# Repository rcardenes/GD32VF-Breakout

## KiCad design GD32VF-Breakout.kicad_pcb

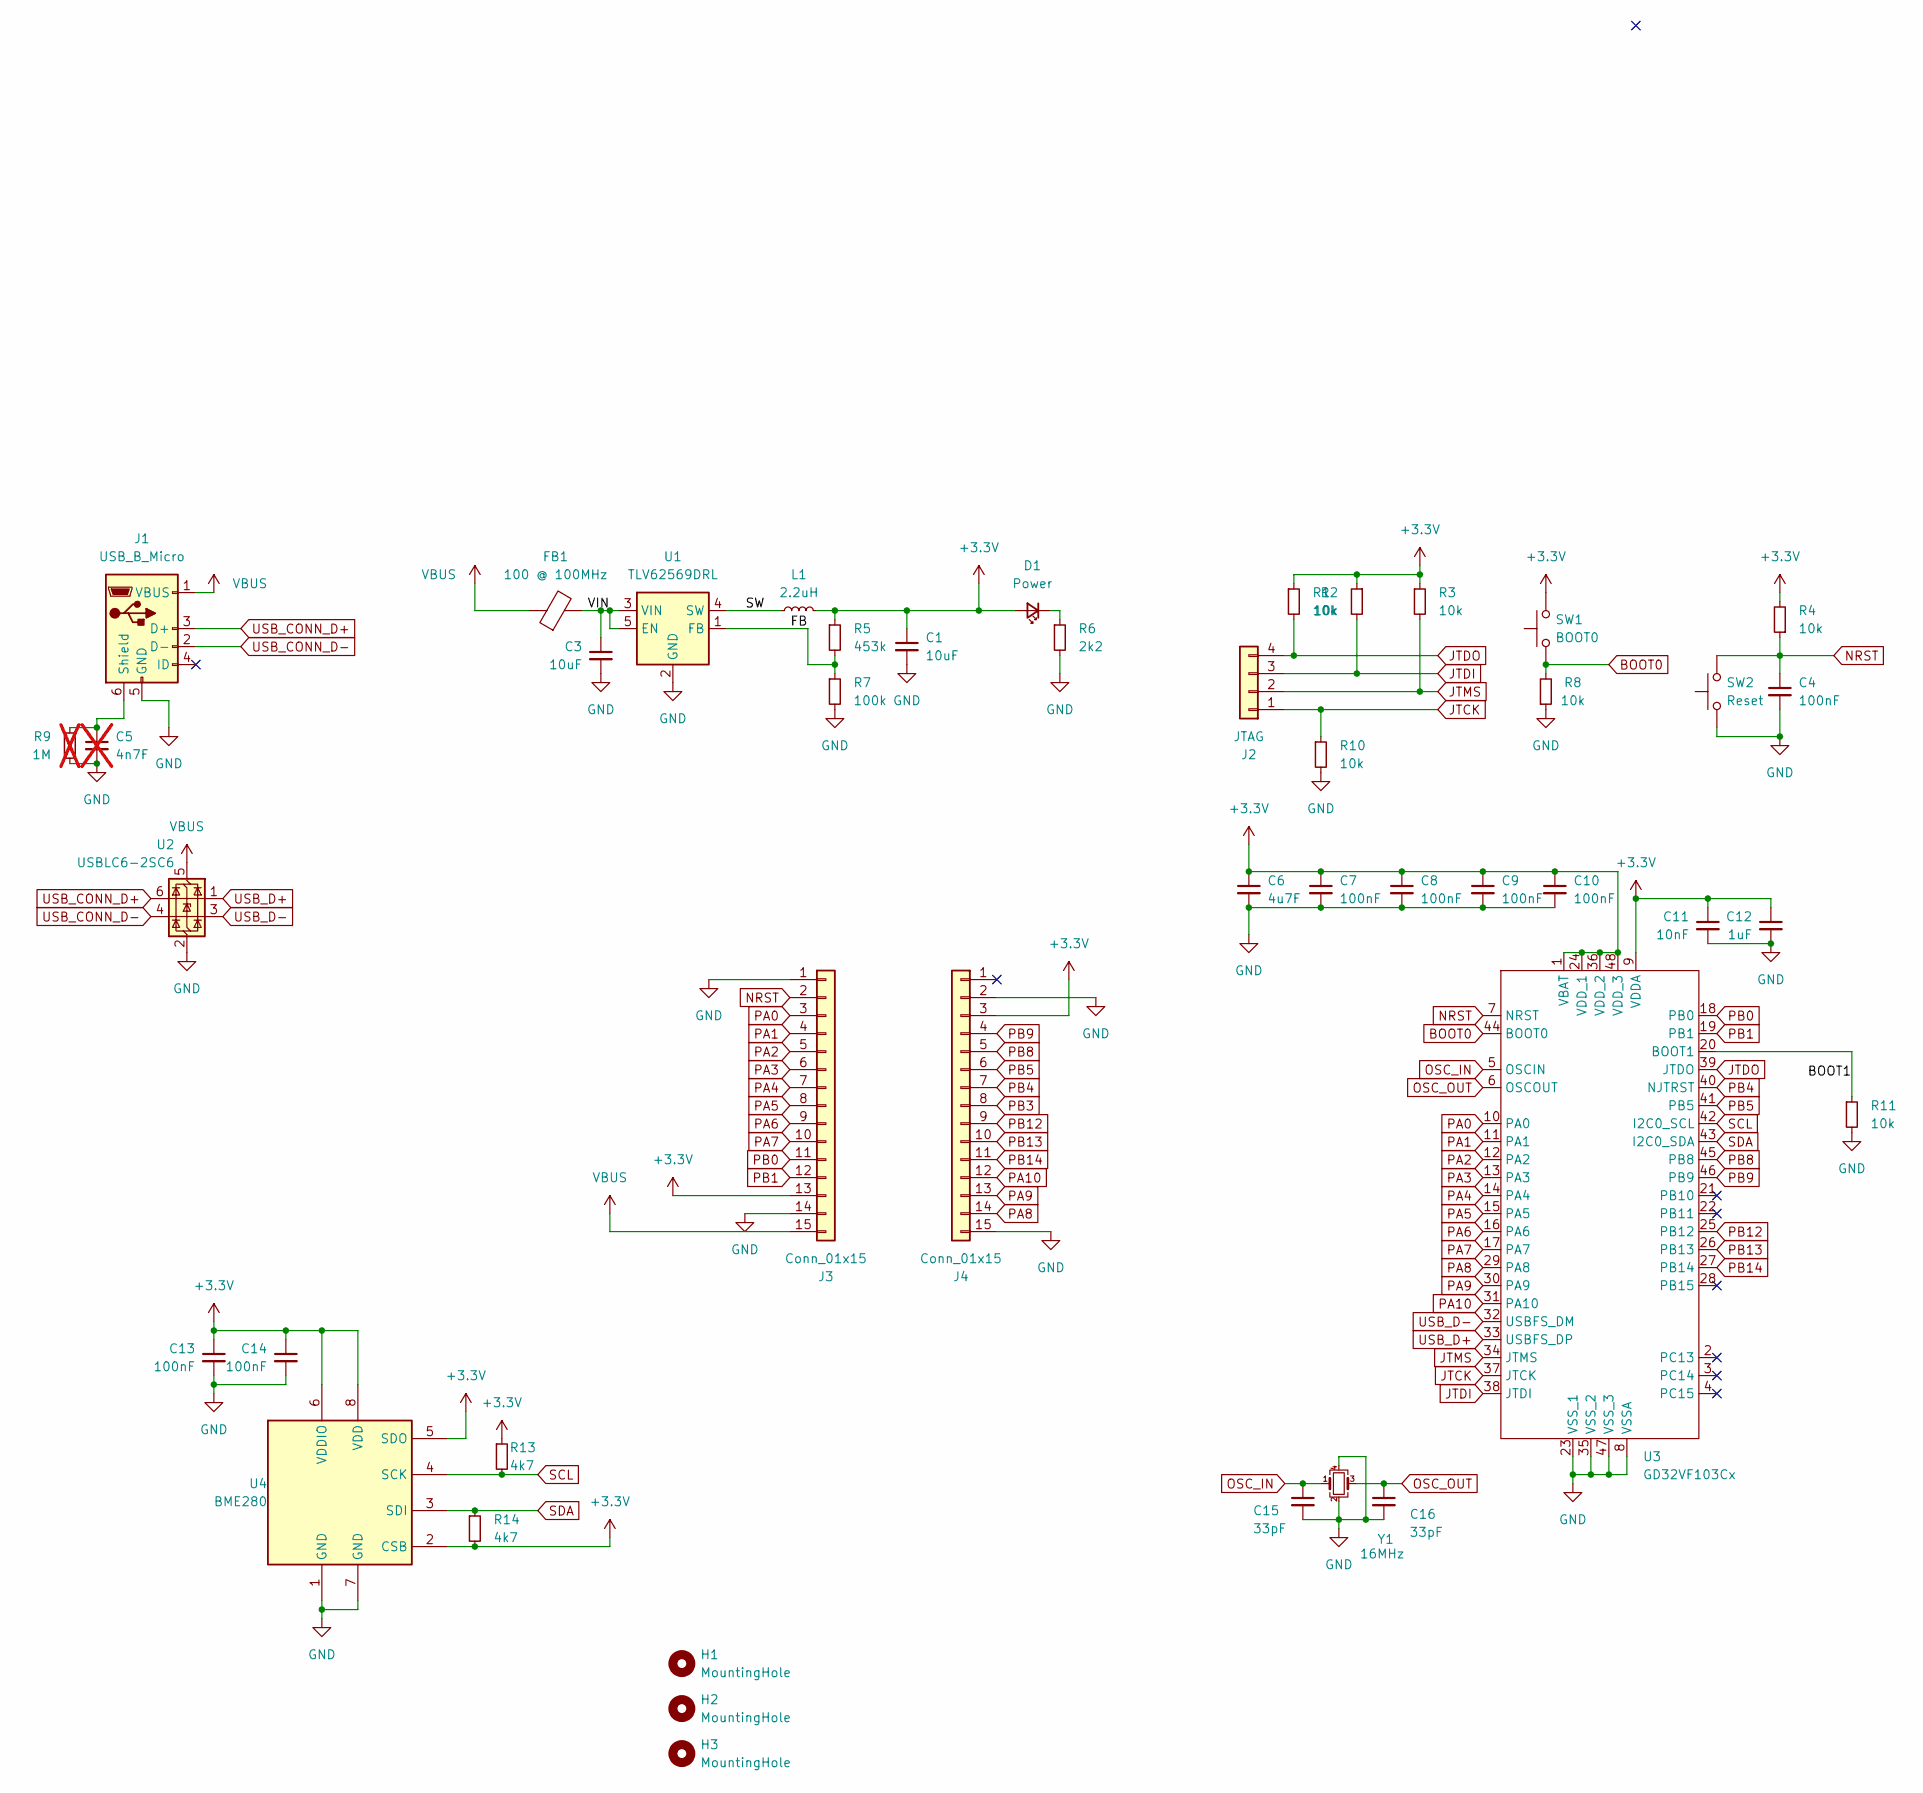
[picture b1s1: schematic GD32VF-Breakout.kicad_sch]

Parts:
C1, C3: 10uF; C_0603_1608Metric; LCSC C19702
C4: 100nF; C_0603_1608Metric; LCSC C1525
C5: 4n7F; C_0603_1608Metric; LCSC C1538; not fitted
C6: 4u7F; C_0603_1608Metric; LCSC C19666
C7, C8, C9, C10: 100nF; C_0402_1005Metric; LCSC C1525
C11: 10nF; C_0402_1005Metric; LCSC C15195
C12: 1uF; C_0603_1608Metric; LCSC C15849
C13, C14: 100nF; C_0402_1005Metric
C15, C16: 33pF; C_0603_1608Metric; LCSC C1554
D1: Power; LED_0805_2012Metric; LCSC C2286
FB1: 100 @ 100MHz; L_1206_3216Metric; LCSC C1015
H1, H2, H3: MountingHole; MountingHole_2.2mm_M2
J1: USB_B_Micro; USB_Micro-B_Amphenol_10118193-0001LF_Horizontal
J2: JTAG; PinHeader_1x04_P2.54mm_Vertical
J3, J4: Conn_01x15; PinHeader_1x15_P2.54mm_Vertical
L1: 2.2uH; L_1210_3225Metric
R1, R2, R3, R10: 10k; R_0603_1608Metric
R4, R8, R11: 10k; R_0603_1608Metric; LCSC C25744
R5: 453k; R_0603_1608Metric
R6: 2k2; R_0603_1608Metric; LCSC C25879
R7: 100k; R_0603_1608Metric
R9: 1M; R_0603_1608Metric; LCSC C26083; not fitted
R13, R14: 4k7; R_0402_1005Metric
SW1: BOOT0; SW_Push_1P1T_NO_CK_KMR2; LCSC C221676
SW2: Reset; SW_Push_1P1T_NO_CK_KMR2; LCSC C221676
U1: TLV62569DRL; SOT-563
U2: USBLC6-2SC6; SOT-23-6; LCSC C2827654
U3: GD32VF103Cx; LQFP-48_7x7mm_P0.5mm
U4: BME280; Bosch_LGA-8_2.5x2.5mm_P0.65mm_ClockwisePinNumbering
Y1: 16MHz; Crystal_SMD_3225-4Pin_3.2x2.5mm; LCSC C9002

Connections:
+3.3V: C1.1, C6.1, C7.1, C8.1, C9.1, C10.1, C11.1, C12.1, C13.1, C14.1, D1.2 (A), J3.13, J4.3, L1.2, R1.1, R2.1, R3.1, R4.2, R5.1, R13.1, R14.2, SW1.2, U3.1 (VBAT), U3.9 (VDDA), U3.24 (VDD_1), U3.36 (VDD_2), U3.48 (VDD_3), U4.2 (CSB), U4.5 (SDO), U4.6 (VDDIO), U4.8 (VDD)
/BOOT1: R11.1, U3.20 (BOOT1)
/FB: R5.2, R7.1, U1.1 (FB)
/SW: L1.1, U1.4 (SW)
/VIN: C3.1, FB1.2, U1.3 (VIN), U1.5 (EN)
BOOT0: R8.2, SW1.1, U3.44 (BOOT0)
GND: C1.2, C3.2, C4.2, C5.2, C6.2, C7.2, C8.2, C9.2, C10.2, C11.2, C12.2, C13.2, C14.2, C15.2, C16.2, J1.5 (GND), J3.1, J3.14, J4.2, J4.15, R6.2, R7.2, R8.1, R9.1, R10.2, R11.2, SW2.1, U1.2 (GND), U2.2 (GND), U3.8 (VSSA), U3.23 (VSS_1), U3.35 (VSS_2), U3.47 (VSS_3), U4.1 (GND), U4.7 (GND), Y1.2, Y1.4
JTCK: J2.1, R10.1, U3.37 (JTCK)
JTDI: J2.3, R2.2, U3.38 (JTDI)
JTDO: J2.4, R1.2, U3.39 (JTDO)
JTMS: J2.2, R3.2, U3.34 (JTMS)
NRST: C4.1, J3.2, R4.1, SW2.2, U3.7 (NRST)
unnamed: D1.1 (K), R6.1
unnamed: C5.1, J1.6 (Shield), R9.2
OSC_IN: C15.1, U3.5 (OSCIN), Y1.1
OSC_OUT: C16.1, U3.6 (OSCOUT), Y1.3
PA0: J3.3, U3.10 (PA0)
PA1: J3.4, U3.11 (PA1)
PA2: J3.5, U3.12 (PA2)
PA3: J3.6, U3.13 (PA3)
PA4: J3.7, U3.14 (PA4)
PA5: J3.8, U3.15 (PA5)
PA6: J3.9, U3.16 (PA6)
PA7: J3.10, U3.17 (PA7)
PA8: J4.14, U3.29 (PA8)
PA9: J4.13, U3.30 (PA9)
PA10: J4.12, U3.31 (PA10)
PB0: J3.11, U3.18 (PB0)
PB1: J3.12, U3.19 (PB1)
PB3: J4.8
PB4: J4.7, U3.40 (NJTRST)
PB5: J4.6, U3.41 (PB5)
PB8: J4.5, U3.45 (PB8)
PB9: J4.4, U3.46 (PB9)
PB12: J4.9, U3.25 (PB12)
PB13: J4.10, U3.26 (PB13)
PB14: J4.11, U3.27 (PB14)
SCL: R13.2, U3.42 (I2C0_SCL), U4.4 (SCK)
SDA: R14.1, U3.43 (I2C0_SDA), U4.3 (SDI)
USB_CONN_D+: J1.3 (D+), U2.6 (I/O1)
USB_CONN_D-: J1.2 (D-), U2.4 (I/O2)
USB_D+: U2.1 (I/O1), U3.33 (USBFS_DP)
USB_D-: U2.3 (I/O2), U3.32 (USBFS_DM)
VBUS: FB1.1, J1.1 (VBUS), J3.15, U2.5 (VBUS)

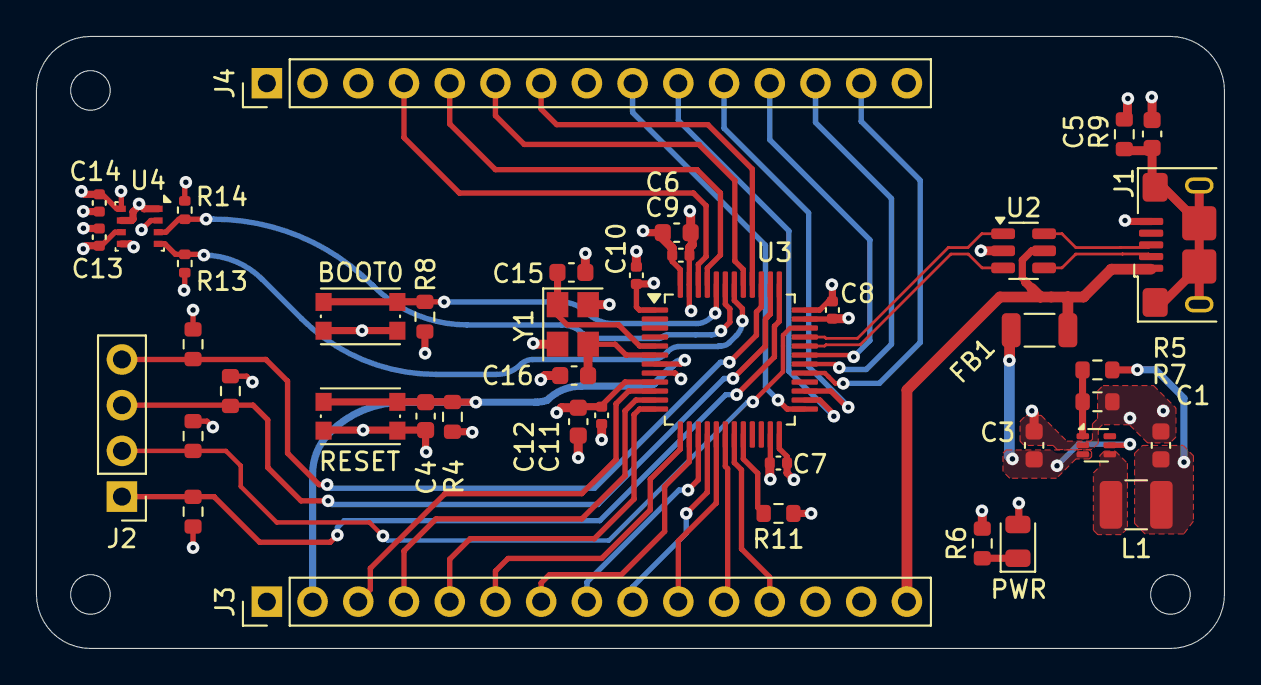
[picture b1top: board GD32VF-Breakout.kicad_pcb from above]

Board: 4 copper layers, 66.0 x 34.0 mm, 45 parts (0 on the bottom side), 43 nets.

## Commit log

2024-11-29 Import project
2024-11-29 Added submodule for local libraries
2024-12-11 First changes
2025-02-08 Full board, as sent for fabrication
